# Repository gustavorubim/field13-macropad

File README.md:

# FIELD 13

An original, editable DIY macropad prototype with 13 MX hot-swap keys, a rotary encoder, a two-axis joystick, an optional touch position and a soldered Raspberry Pi Pico W.

**A0 design prototype. Not yet a fabrication release.** The files are real CAD, PCB and source code, but there has been no physical assembly, electrical bring-up, radio test or print-fit test. Software checks and CAD clearances cannot replace those tests.

## What is here

| Area | Deliverable |
|---|---|
| Electronics | Editable KiCad schematic, two-layer routed board, custom symbol/footprint libraries, source links and check reports |
| Mechanical | Native FreeCAD full assembly, STEP, printable case/plate/knob/feet, fit coupon and reproducible parameters |
| Visuals | Direct CAD preview, studio front/top/rear views, exploded view and editable Blender studio scene |
| Firmware | Code-configured keymaps/layers, encoder/media controls, joystick arrows/mouse, USB HID, optional authenticated Windows Wi-Fi companion |
| Integration | Optional Microbridge local serial companion for six agent focus keys and LED feedback; macOS daemon baseline |
| Build | Exact-part BOM, pin map, assembly instructions, bench tests and explicit remaining validation gates |

The layout follows the requested control arrangement: encoder and joystick around two top keys, two rows of four keys, and three bottom keys next to the optional touch position. All keycaps are standard 1U. The enclosure is 108 × 122 mm, with rounded corners, rear port access, underside fasteners and TPU feet.

## Start here

1. Read [the current verification status](docs/verification.md)
2. Inspect the KiCad project in `electronics/` and [electrical notes](docs/electronics.md)
3. Review [mechanical dimensions and print-fit gates](docs/mechanical.md)
4. Use the [BOM](docs/BOM.csv) and [assembly guide](docs/assembly.md)
5. Configure [firmware and host companions](docs/firmware.md)

## Editable sources

- `electronics/macropad.kicad_sch` and the final routed `.kicad_pcb` named in the electrical notes
- `mechanical/FIELD13_assembly.FCStd` and `FIELD13_assembly.step`
- `mechanical/parameters.json` plus `scripts/generate_mechanical.py`
- `mechanical/stl/` for printable parts, including the fit coupon
- `mechanical/FIELD13_studio.blend` plus `scripts/render_blender.py`
- `firmware/config.py` for keymaps, layers, encoder direction, joystick calibration and transport

The FreeCAD document has named editable solids, design-profile sketches and a dimension reference sheet. Regenerate changed dimensions from the JSON rather than assuming that changing the displayed sheet rebuilds the BRep solids. Purchased parts use documented clearance envelopes; not every small SMT detail is reproduced in CAD.

## Connectivity limits

USB HID is the default. Pico W Wi-Fi mode uses a separately started Windows companion and explicitly configured pairing key. It is not Bluetooth HID. CircuitPython's Pico W target does not provide CYW43 BLE HID in this build. No credentials are included, and no host service installs itself.

The optional Microbridge adapter is separate from the Windows Wi-Fi companion. It targets the pinned upstream protocol and only focuses/open assigned agent slots and receives status colors. It does not impersonate the commercial device's USB identity, approve actions, reject requests or synthesize unsupported daemon controls.

Power is USB or a finished external USB power bank. There is no bare lithium cell, charger or unprotected battery circuit. The microphone is a reserved connector/bay, not a tested microphone or USB-audio implementation. Optional touch/RGB peripherals require their own physical validation.

## Gallery

## Reproduce checks

```sh
python -m unittest discover -s tests/firmware -v
python -m compileall -q firmware
/usr/bin/python3 scripts/generate_mechanical.py
HOME=/tmp/macropad-home kicad-cli sch erc electronics/macropad.kicad_sch
```

The electrical notes identify the final PCB, final ERC/DRC commands and report files. Generated file paths are relative to this repository except where a tool requires its system library path. KiCad 9.0.2, FreeCAD 1.0 and Blender 4.3.2 were used in the development VM.

## Sources and credit

The requested arrangement was inspired by [OpenAI Supply Co. × Work Louder](https://openai.com/supply/co-lab/work-louder/). FIELD 13 is an independent DIY design, not an official product, clone firmware, compatibility certification or endorsement.

Component geometry and electrical constraints are based on the manufacturer sources linked in the BOM and electrical notes. Optional Microbridge interoperability is pinned to [DevVig/microbridge, fcd0aba](https://github.com/DevVig/microbridge/tree/fcd0aba7a4fa360ca8690681bd7b049fa3682f10). Third-party datasheets and external executable tools are not republished in this repository.

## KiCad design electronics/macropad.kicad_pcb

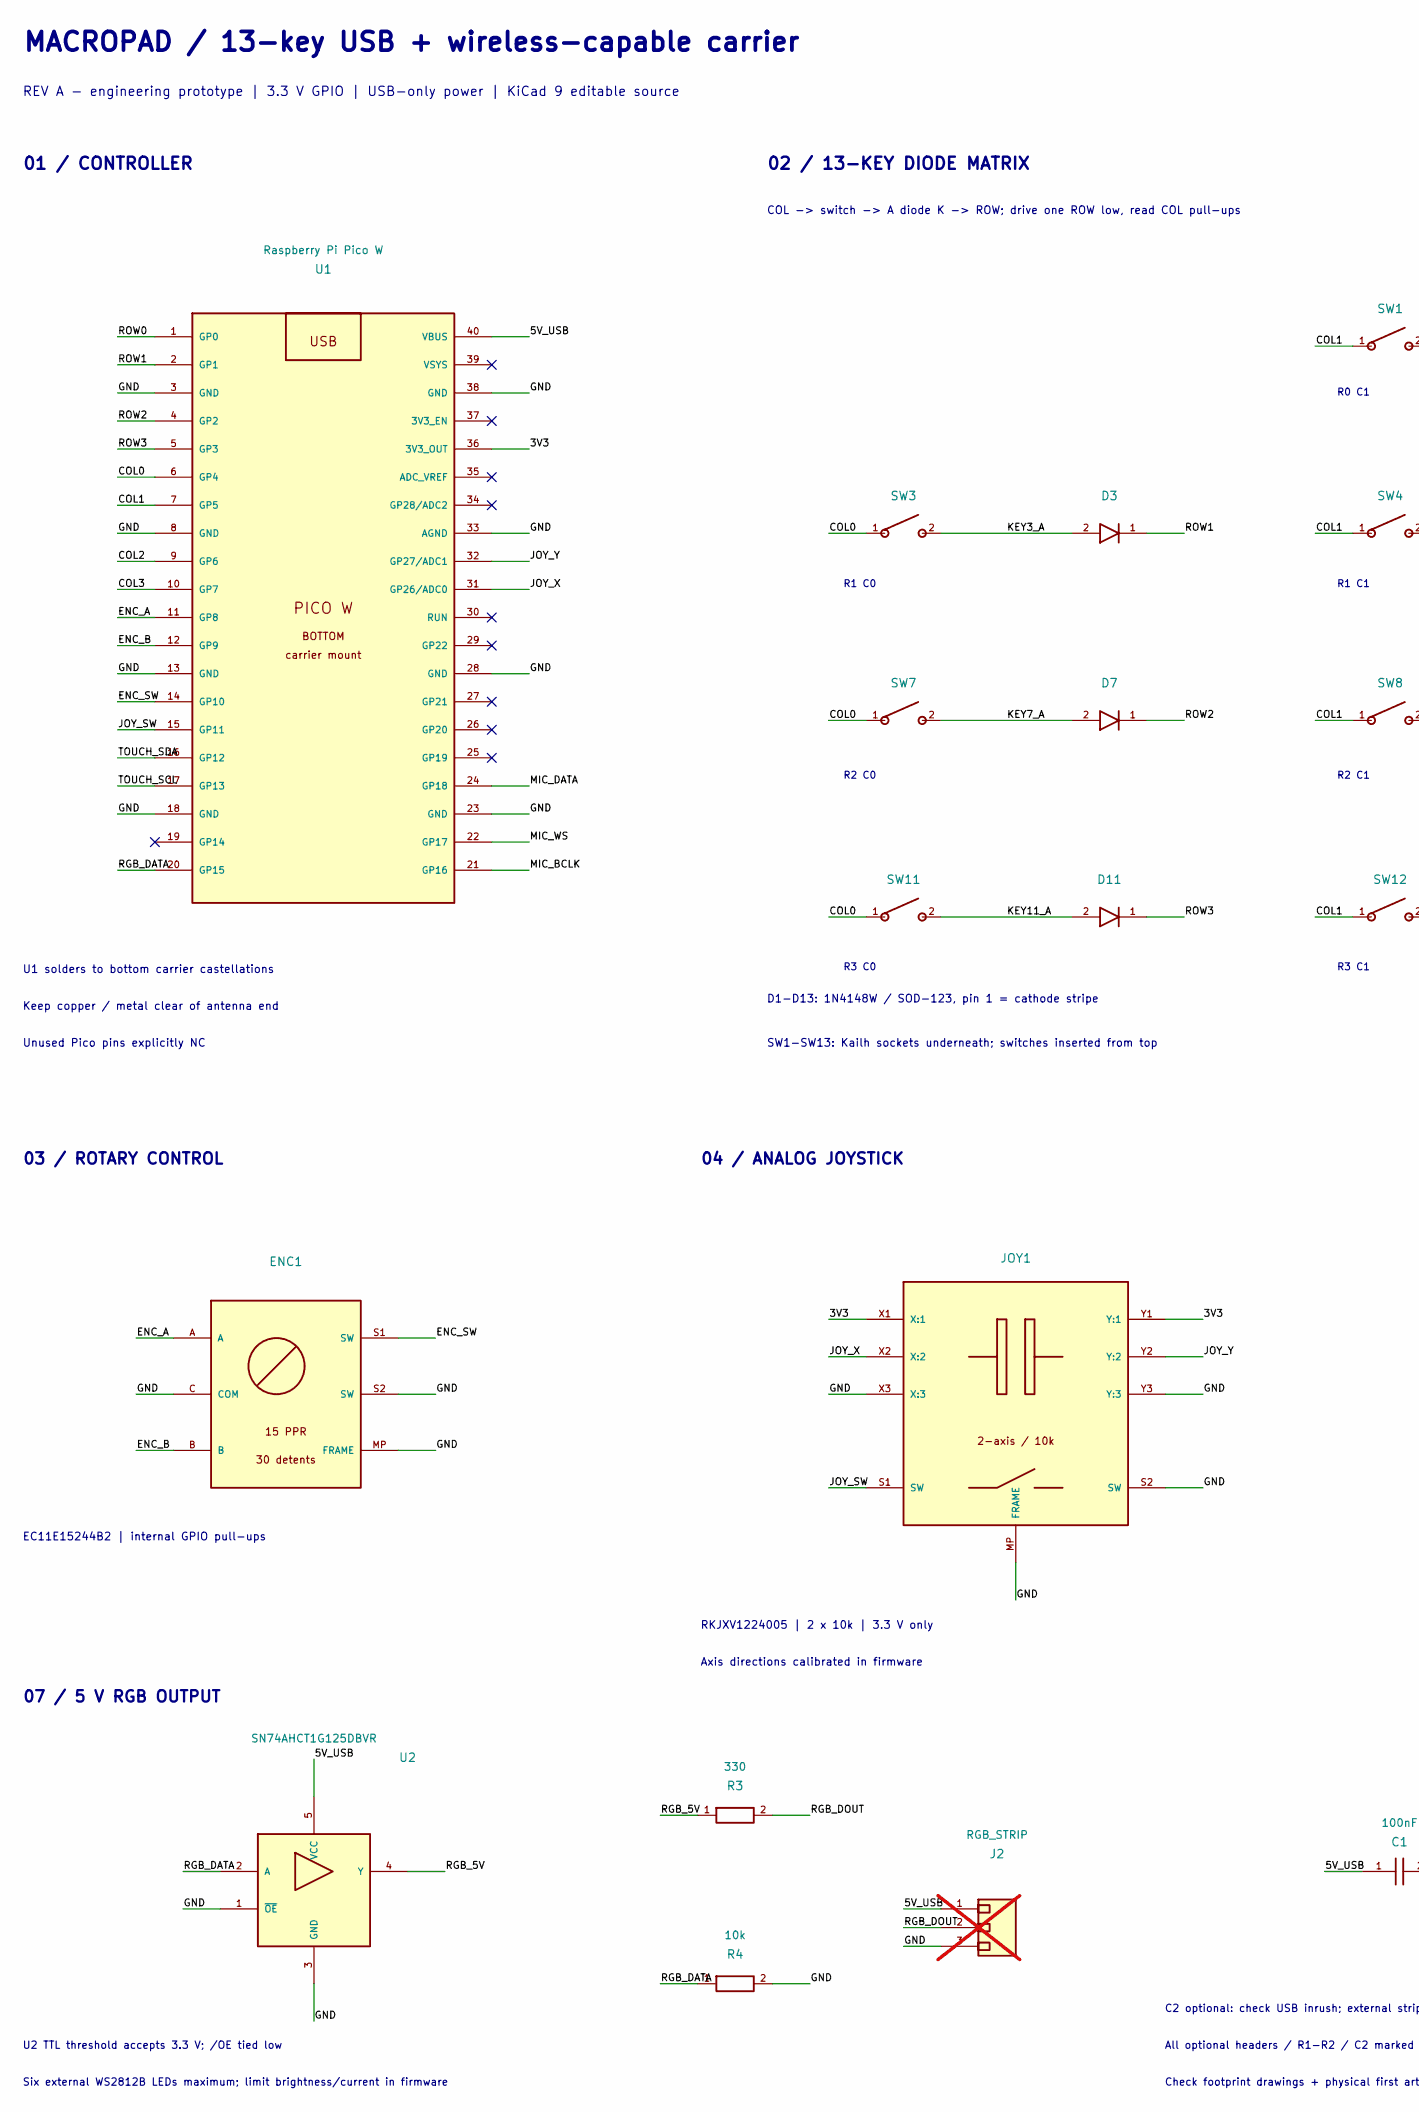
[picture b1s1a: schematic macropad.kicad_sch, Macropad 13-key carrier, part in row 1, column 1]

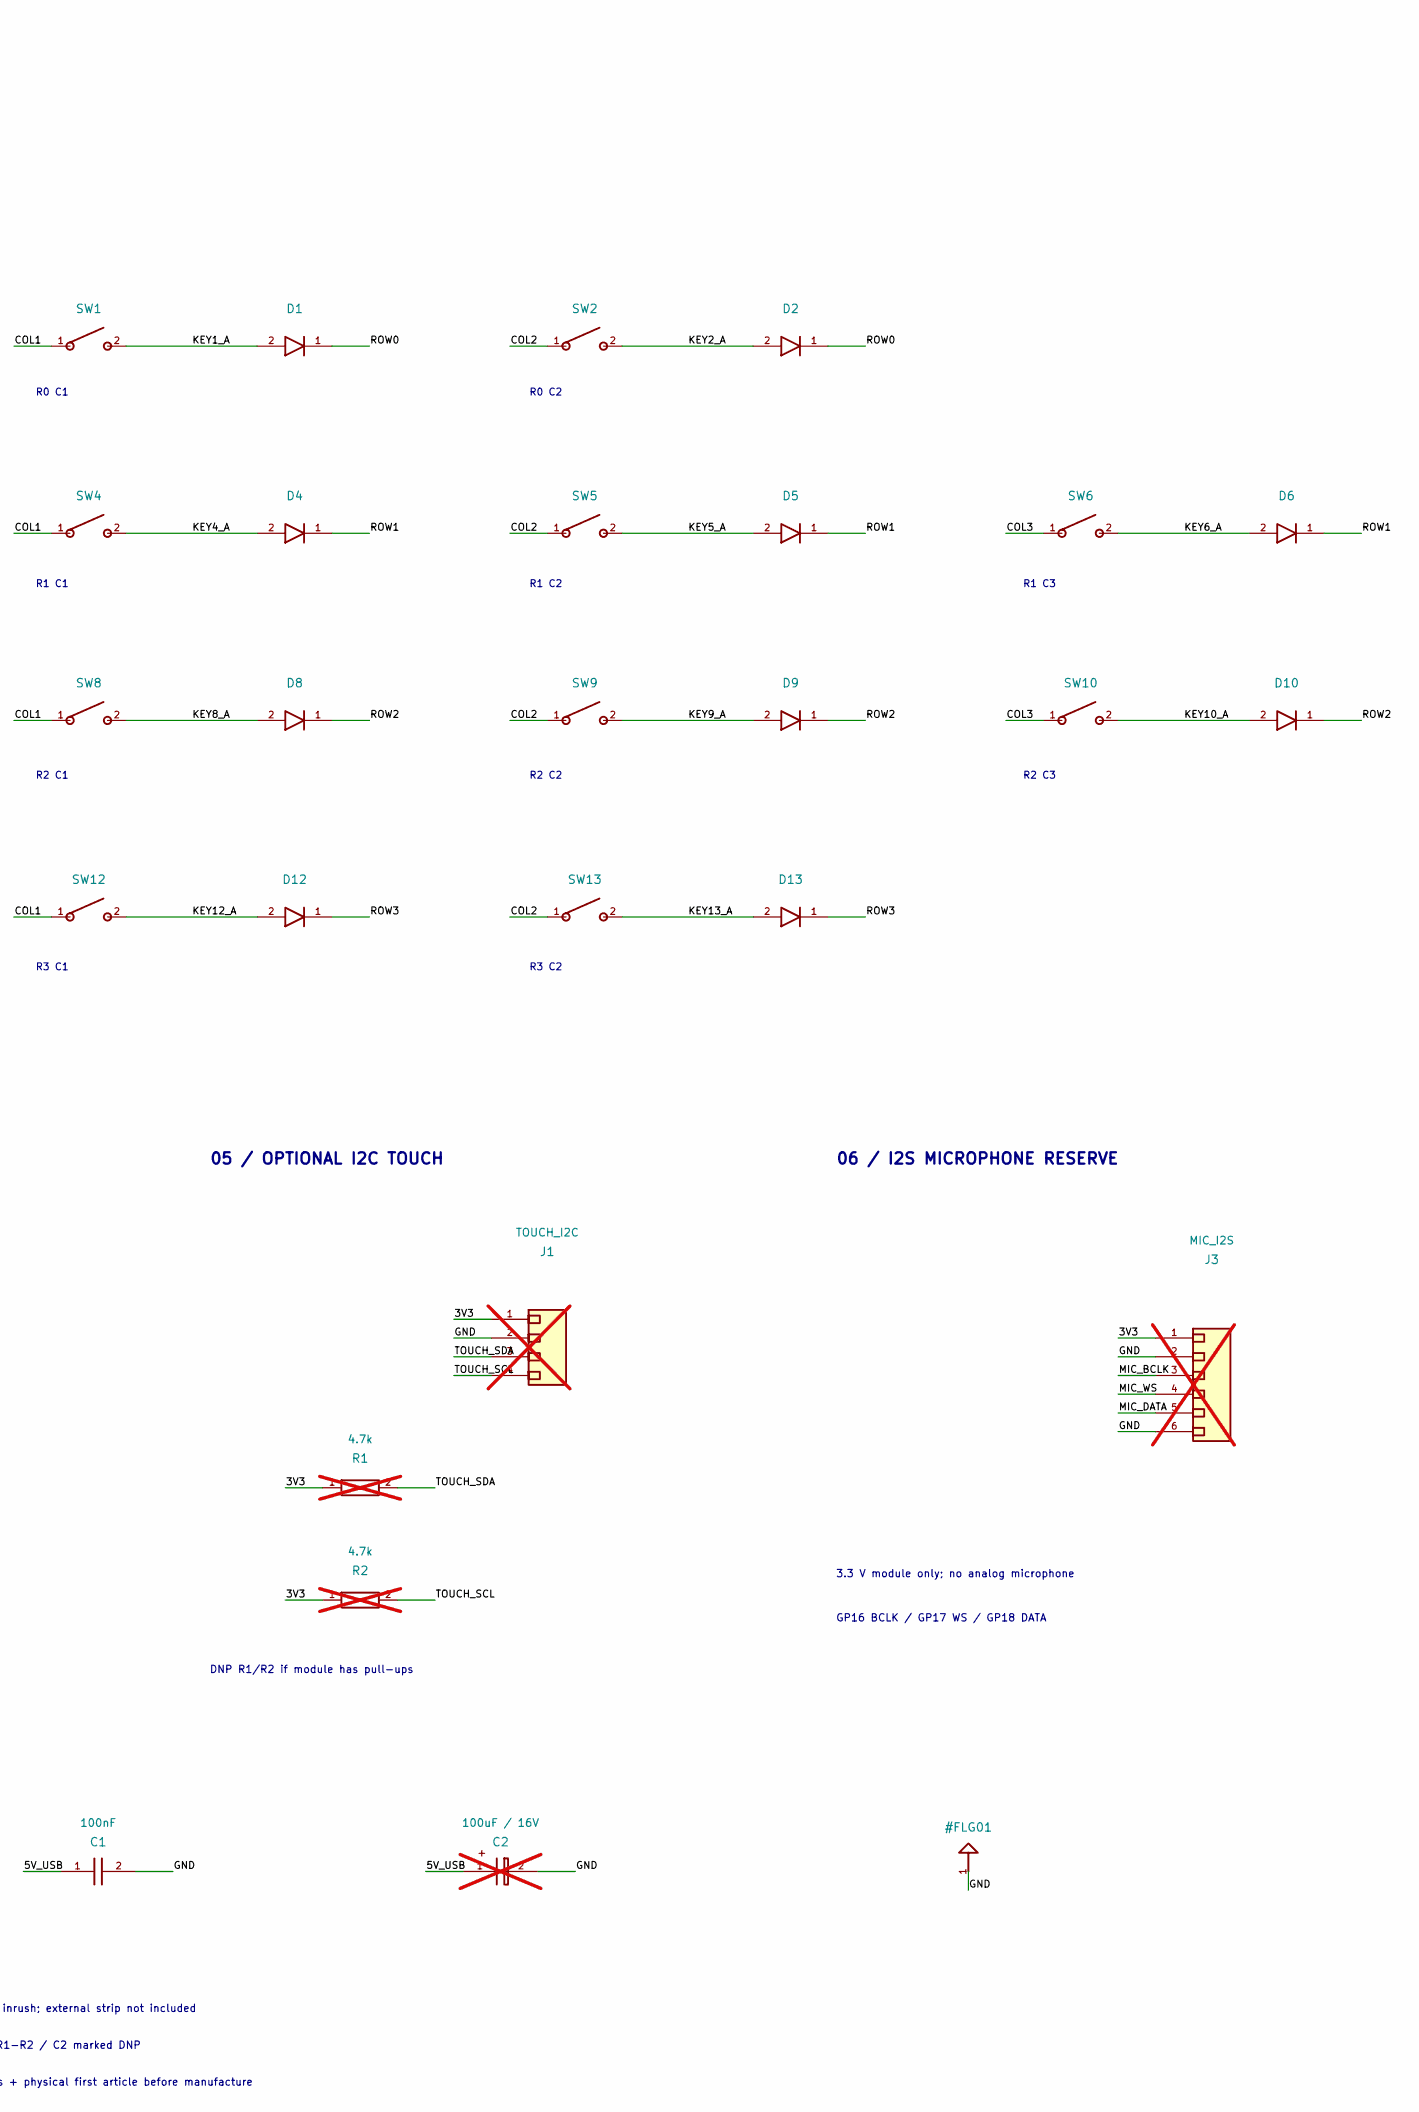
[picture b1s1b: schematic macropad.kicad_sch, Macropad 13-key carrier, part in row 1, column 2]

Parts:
C1: 100nF; C_0603_1608Metric; MPN GRM188R72A104KA35D
C2: 100uF / 16V; CP_Elec_6.3x5.8; MPN EEE-FK1C101P; not fitted
D1, D2, D3, D4, D5, D6, D7, D8, D9, D10, D11, D12, D13: 1N4148W; D_SOD-123; MPN 1N4148W-7-F
ENC1: EC11E15244B2; RotaryEncoder_Alps_EC11E-Switch_Vertical_H20mm; MPN EC11E15244B2
J1: TOUCH_I2C; PinHeader_1x04_P2.54mm_Vertical; MPN TSW-104-07-G-S; not fitted
J2: RGB_STRIP; PinHeader_1x03_P2.54mm_Vertical; MPN TSW-103-07-G-S; not fitted
J3: MIC_I2S; PinHeader_1x06_P2.54mm_Vertical; MPN TSW-106-07-G-S; not fitted
JOY1: RKJXV1224005; Joystick_RKJXV1224005; MPN RKJXV1224005
R1, R2: 4.7k; R_0603_1608Metric; MPN RC0603FR-074K7L; not fitted
R3: 330; R_0603_1608Metric; MPN RC0603FR-07330RL
R4: 10k; R_0603_1608Metric; MPN RC0603FR-0710KL
SW1, SW2, SW3, SW4, SW5, SW6, SW7, SW8, SW9, SW10, SW11, SW12, SW13: MX hot-swap; MX_Hotswap_CPG151101S11_16; MPN CPG151101S11-16
U1: Raspberry Pi Pico W; PicoW_Castellated; MPN SC0918
U2: SN74AHCT1G125DBVR; SOT-23-5; MPN SN74AHCT1G125DBVR

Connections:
/3V3: J1.1, J3.1, JOY1.X1 (X:1), JOY1.Y1 (Y:1), R1.1, R2.1, U1.36 (3V3_OUT)
/5V_USB: C1.1, C2.1 (+), J2.1, U1.40 (VBUS), U2.5 (VCC)
/COL0: SW3.1, SW7.1, SW11.1, U1.6 (GP4)
/COL1: SW1.1, SW4.1, SW8.1, SW12.1, U1.7 (GP5)
/COL2: SW2.1, SW5.1, SW9.1, SW13.1, U1.9 (GP6)
/COL3: SW6.1, SW10.1, U1.10 (GP7)
/ENC_A: ENC1.A, U1.11 (GP8)
/ENC_B: ENC1.B, U1.12 (GP9)
/ENC_SW: ENC1.S1 (SW), U1.14 (GP10)
/GND: C1.2, C2.2 (-), ENC1.C (COM), ENC1.MP (FRAME), ENC1.S2 (SW), J1.2, J2.3, J3.2, J3.6, JOY1.MP (FRAME), JOY1.S2 (SW), JOY1.X3 (X:3), JOY1.Y3 (Y:3), R4.2, U1.3 (GND), U1.8 (GND), U1.13 (GND), U1.18 (GND), U1.23 (GND), U1.28 (GND), U1.33 (AGND), U1.38 (GND), U2.1 (~OE), U2.3 (GND)
/JOY_SW: JOY1.S1 (SW), U1.15 (GP11)
/JOY_X: JOY1.X2 (X:2), U1.31 (GP26/ADC0)
/JOY_Y: JOY1.Y2 (Y:2), U1.32 (GP27/ADC1)
/KEY1_A: D1.2 (A), SW1.2
/KEY2_A: D2.2 (A), SW2.2
/KEY3_A: D3.2 (A), SW3.2
/KEY4_A: D4.2 (A), SW4.2
/KEY5_A: D5.2 (A), SW5.2
/KEY6_A: D6.2 (A), SW6.2
/KEY7_A: D7.2 (A), SW7.2
/KEY8_A: D8.2 (A), SW8.2
/KEY9_A: D9.2 (A), SW9.2
/KEY10_A: D10.2 (A), SW10.2
/KEY11_A: D11.2 (A), SW11.2
/KEY12_A: D12.2 (A), SW12.2
/KEY13_A: D13.2 (A), SW13.2
/MIC_BCLK: J3.3, U1.21 (GP16)
/MIC_DATA: J3.5, U1.24 (GP18)
/MIC_WS: J3.4, U1.22 (GP17)
/RGB_5V: R3.1, U2.4 (Y)
/RGB_DATA: R4.1, U1.20 (GP15), U2.2 (A)
/RGB_DOUT: J2.2, R3.2
/ROW0: D1.1 (K), D2.1 (K), U1.1 (GP0)
/ROW1: D3.1 (K), D4.1 (K), D5.1 (K), D6.1 (K), U1.2 (GP1)
/ROW2: D7.1 (K), D8.1 (K), D9.1 (K), D10.1 (K), U1.4 (GP2)
/ROW3: D11.1 (K), D12.1 (K), D13.1 (K), U1.5 (GP3)
/TOUCH_SCL: J1.4, R2.2, U1.17 (GP13)
/TOUCH_SDA: J1.3, R1.2, U1.16 (GP12)

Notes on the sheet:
MACROPAD / 13-key USB + wireless-capable carrier
REV A - engineering prototype | 3.3 V GPIO | USB-only power | KiCad 9 editable source
01 / CONTROLLER
U1 solders to bottom carrier castellations
Keep copper / metal clear of antenna end
Unused Pico pins explicitly NC
02 / 13-KEY DIODE MATRIX
COL -> switch -> A diode K -> ROW; drive one ROW low, read COL pull-ups
R0 C1
R0 C2
R1 C0
R1 C1
R1 C2
R1 C3
R2 C0
R2 C1
R2 C2
R2 C3
R3 C0
R3 C1
R3 C2
D1-D13: 1N4148W / SOD-123, pin 1 = cathode stripe
SW1-SW13: Kailh sockets underneath; switches inserted from top
03 / ROTARY CONTROL
EC11E15244B2 | internal GPIO pull-ups
04 / ANALOG JOYSTICK
RKJXV1224005 | 2 x 10k | 3.3 V only
Axis directions calibrated in firmware
05 / OPTIONAL I2C TOUCH
DNP R1/R2 if module has pull-ups
06 / I2S MICROPHONE RESERVE
3.3 V module only; no analog microphone
GP16 BCLK / GP17 WS / GP18 DATA
07 / 5 V RGB OUTPUT
U2 TTL threshold accepts 3.3 V; /OE tied low
Six external WS2812B LEDs maximum; limit brightness/current in firmware
C2 optional: check USB inrush; external strip not included
All optional headers / R1-R2 / C2 marked DNP
Check footprint drawings + physical first article before manufacture

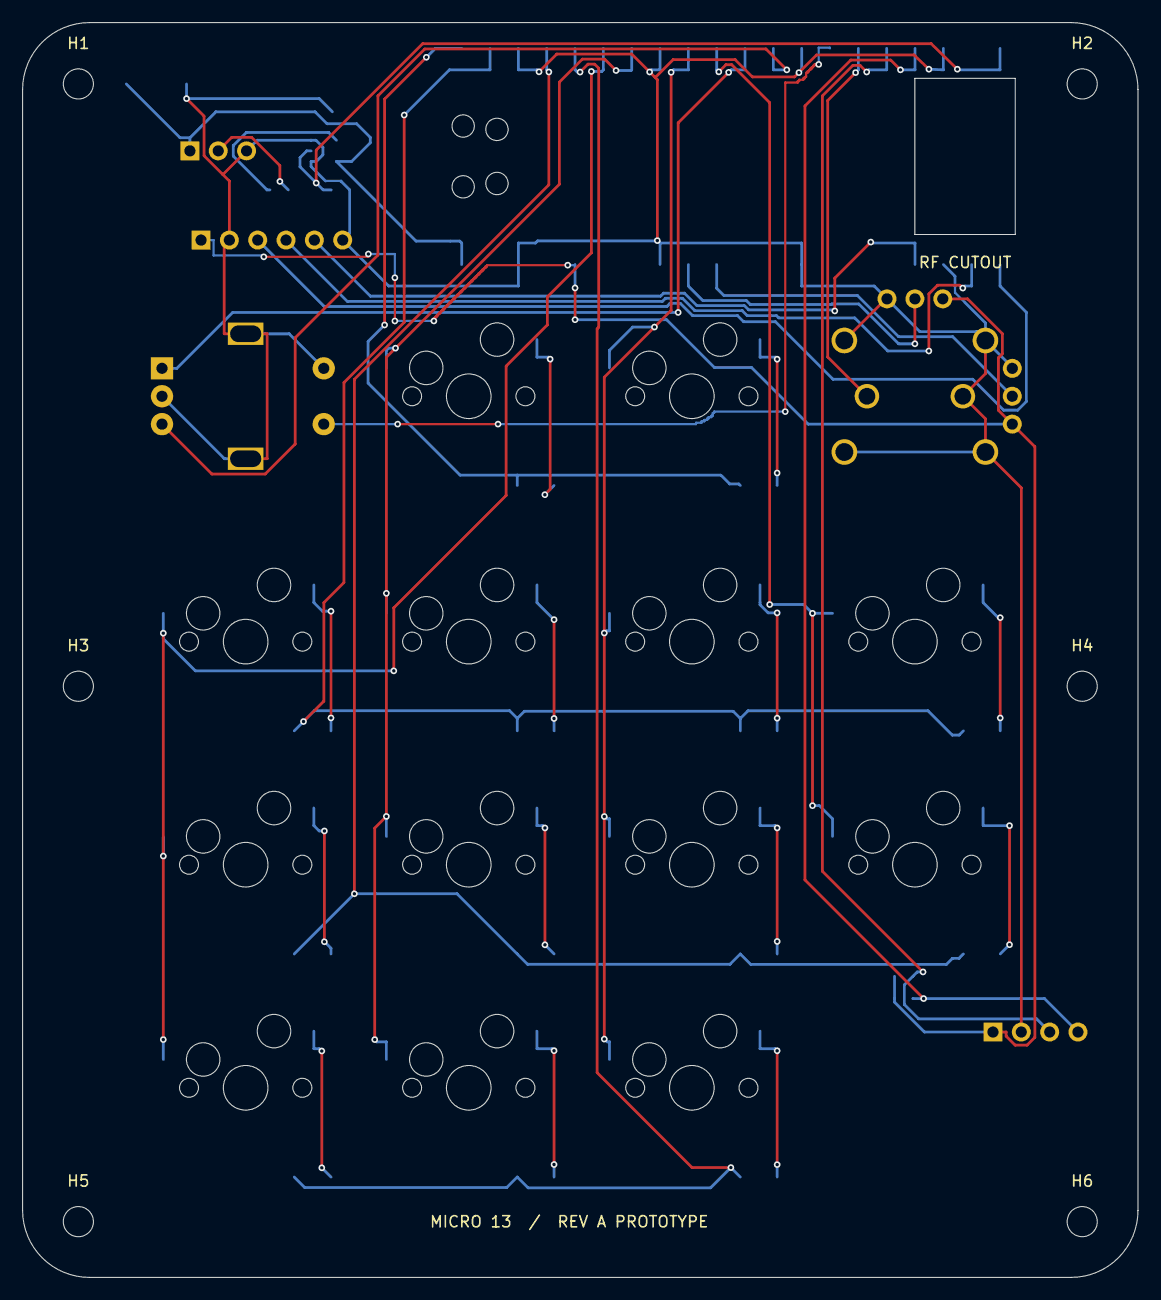
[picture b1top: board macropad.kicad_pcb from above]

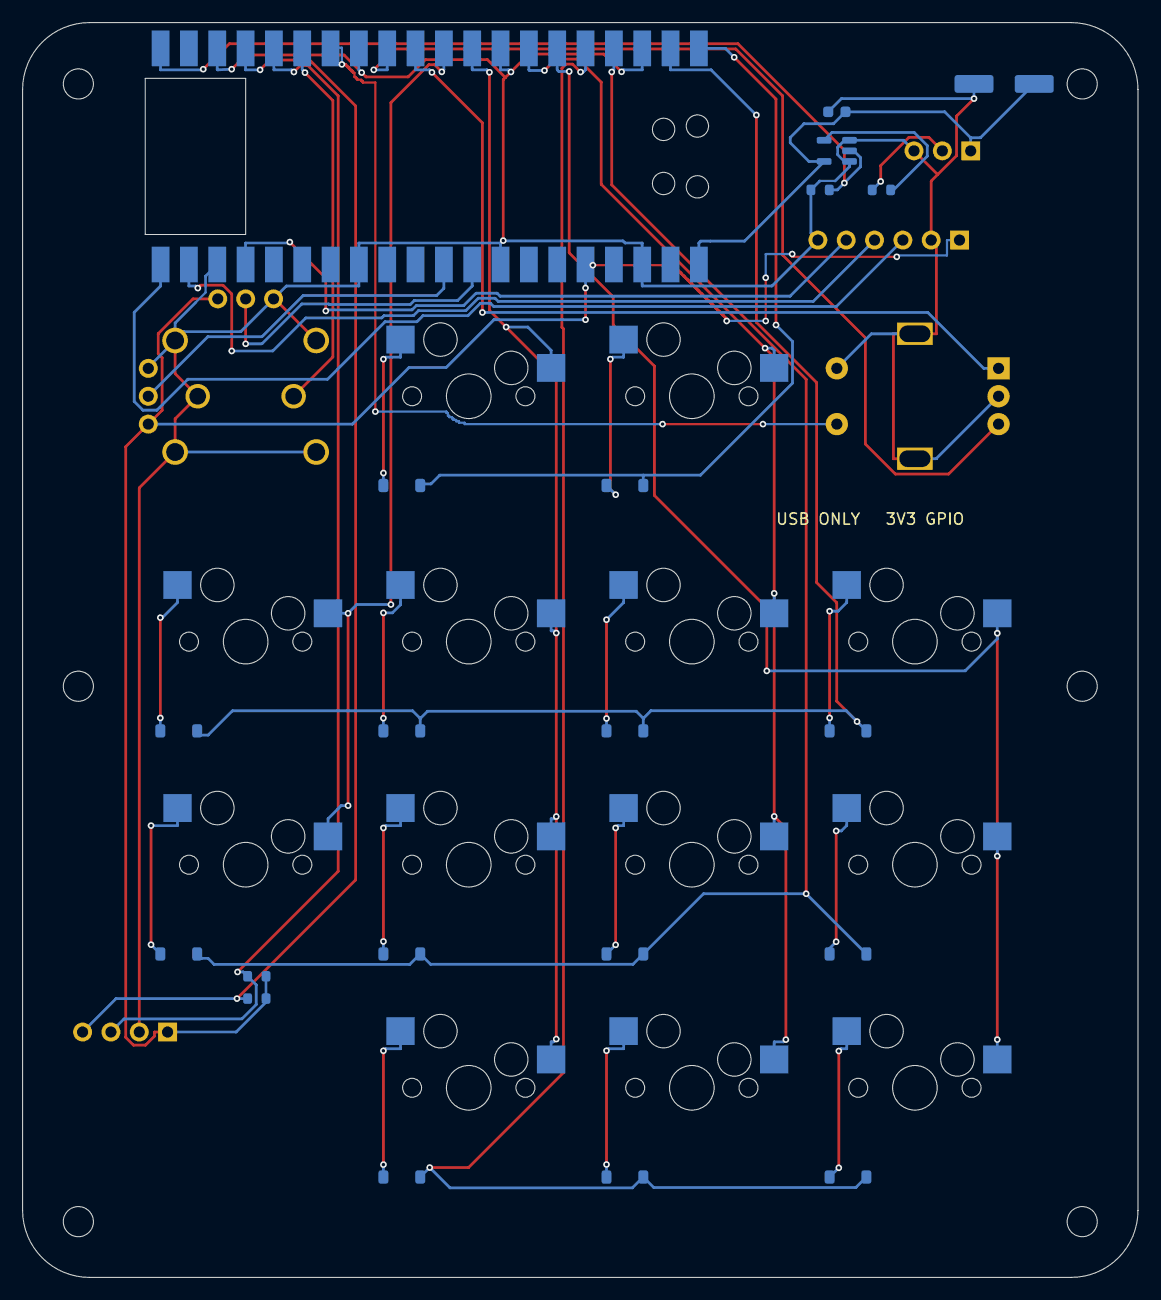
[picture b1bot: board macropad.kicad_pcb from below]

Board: 2 copper layers, 100.0 x 112.5 mm, 45 parts (34 on the bottom side), 38 nets.

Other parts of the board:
H1, H2, H3, H4, H5, H6: MountingHole_2.7mm_M2.5

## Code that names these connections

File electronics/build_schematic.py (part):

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 comp('D'+str(i),'1N4148W','Diode_SMD:D_SOD-123',{'1':f'ROW{r}','2':f'KEY{i}_A'},manufacturer='Diodes Incorporated',mpn='1N4148W-7-F',source='https://www.diodes.com/assets/Datasheets/ds12019.pdf',side='B',description='Pin 1 cathode toward row; pin 2 anode toward switch')
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for ref,n,pins,value in [('J1',4,{1:'3V3',2:'GND',3:'TOUCH_SDA',4:'TOUCH_SCL'},'TOUCH_I2C'),('J2',3,{1:'5V_USB',2:'RGB_DOUT',3:'GND'},'RGB_STRIP'),('J3',6,{1:'3V3',2:'GND',3:'MIC_BCLK',4:'MIC_WS',5:'MIC_DATA',6:'GND'},'MIC_I2S')]:
 comp(ref,value,f'Connector_PinHeader_2.54mm:PinHeader_1x0{n}_P2.54mm_Vertical',pins,manufacturer='Samtec',mpn=f'TSW-10{n}-07-G-S',source=f'https://www.samtec.com/products/tsw',side='F',optional=True,description='Optional 2.54 mm header; external peripherals not on PCB')
for ref,val,net1,net2,mpn in [('R1','4.7k','3V3','TOUCH_SDA','RC0603FR-074K7L'),('R2','4.7k','3V3','TOUCH_SCL','RC0603FR-074K7L'),('R3','330','RGB_5V','RGB_DOUT','RC0603FR-07330RL')]:
 comp(ref,val,'Resistor_SMD:R_0603_1608Metric',{'1':net1,'2':net2},manufacturer='Yageo',mpn=mpn,source='https://www.yageo.com/en/PartSearch',side='B',optional=ref!='R3',description='I2C pull-up: DNP if peripheral already fitted with pull-ups' if ref!='R3' else 'RGB data series damping resistor')
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comp('C1','100nF','Capacitor_SMD:C_0603_1608Metric',{'1':'5V_USB','2':'GND'},manufacturer='Murata',mpn='GRM188R72A104KA35D',source='https://www.murata.com/en-us/products/productdetail?partno=GRM188R71C104KA01%23',side='B',description='100V X7R bypass adjacent to U2')
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comp('R4','10k','Resistor_SMD:R_0603_1608Metric',{'1':'RGB_DATA','2':'GND'},manufacturer='Yageo',mpn='RC0603FR-0710KL',source='https://www.yageo.com/en/PartSearch',side='B',description='Pull-down holds AHCT input low during reset or high-impedance Pico GPIO state')
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
if not (E/'net_manifest.json').exists(): (E/'net_manifest.json').write_text(json.dumps(manifest,indent=2)+'\n')
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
